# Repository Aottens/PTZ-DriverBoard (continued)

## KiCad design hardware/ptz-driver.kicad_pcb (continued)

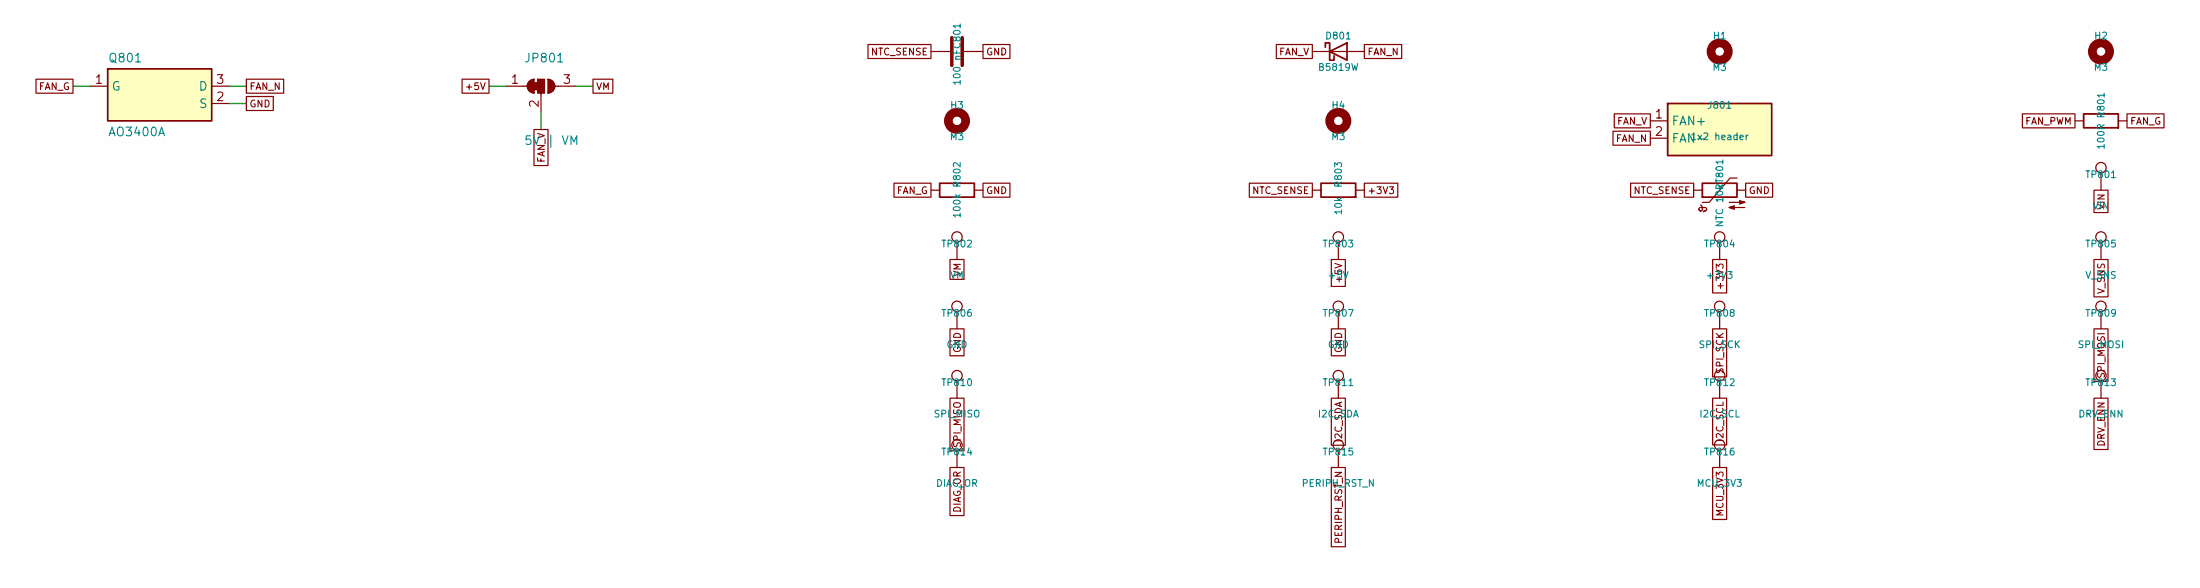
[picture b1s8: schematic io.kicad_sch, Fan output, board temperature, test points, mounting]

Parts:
C801: 100 nF; C_0603_1608Metric; LCSC C14663
D801: B5819W; D_SOD-123; MPN B5819W; LCSC C8598
H1, H2, H3, H4: M3; MountingHole_3.2mm_M3
J801: 1x2 header; PinHeader_1x02_P2.54mm_Vertical
JP801: 5V | VM; SolderJumper-3_P1.3mm_Bridged12_RoundedPad1.0x1.5mm
Q801: AO3400A; SOT-23; MPN AO3400A; LCSC C20917
R801: 100R; R_0603_1608Metric; LCSC C22775
R802: 100k; R_0603_1608Metric; LCSC C25803
R803: 10k; R_0603_1608Metric; LCSC C25804
RT801: NTC 10k; R_0603_1608Metric; MPN KNTC0603/10KF3950; LCSC C2892547
TP801: VIN; TestPoint_D1.5
TP802: VM; TestPoint_D1.5
TP803: +5V; TestPoint_D1.5
TP804: +3V3; TestPoint_D1.5
TP805: V_SNS; TestPoint_D1.5
TP806, TP807: GND; TestPoint_D1.5
TP808: SPI_SCK; TestPoint_D1.5
TP809: SPI_MOSI; TestPoint_D1.5
TP810: SPI_MISO; TestPoint_D1.5
TP811: I2C_SDA; TestPoint_D1.5
TP812: I2C_SCL; TestPoint_D1.5
TP813: DRV_ENN; TestPoint_D1.5
TP814: DIAG_OR; TestPoint_D1.5
TP815: PERIPH_RST_N; TestPoint_D1.5
TP816: MCU_3V3; TestPoint_D1.5

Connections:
+3V3: R803.2, TP804.1; also elsewhere on the board
DRV_ENN: TP813.1; also elsewhere on the board
FAN_G: Q801.1 (G), R801.2, R802.1
FAN_N: D801.2 (A), J801.2 (FAN-), Q801.3 (D)
FAN_PWM: R801.1; also elsewhere on the board
GND: C801.2, Q801.2 (S), R802.2, RT801.2, TP806.1, TP807.1; also elsewhere on the board
I2C_SCL: TP812.1; also elsewhere on the board
I2C_SDA: TP811.1; also elsewhere on the board
MCU_3V3: TP816.1; also elsewhere on the board
NTC_SENSE: C801.1, R803.1, RT801.1; also elsewhere on the board
PERIPH_RST_N: TP815.1; also elsewhere on the board
SPI_MISO: TP810.1; also elsewhere on the board
SPI_MOSI: TP809.1; also elsewhere on the board
SPI_SCK: TP808.1; also elsewhere on the board
VIN: TP801.1; also elsewhere on the board
VM: JP801.3 (B), TP802.1; also elsewhere on the board
V_SNS: TP805.1; also elsewhere on the board

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
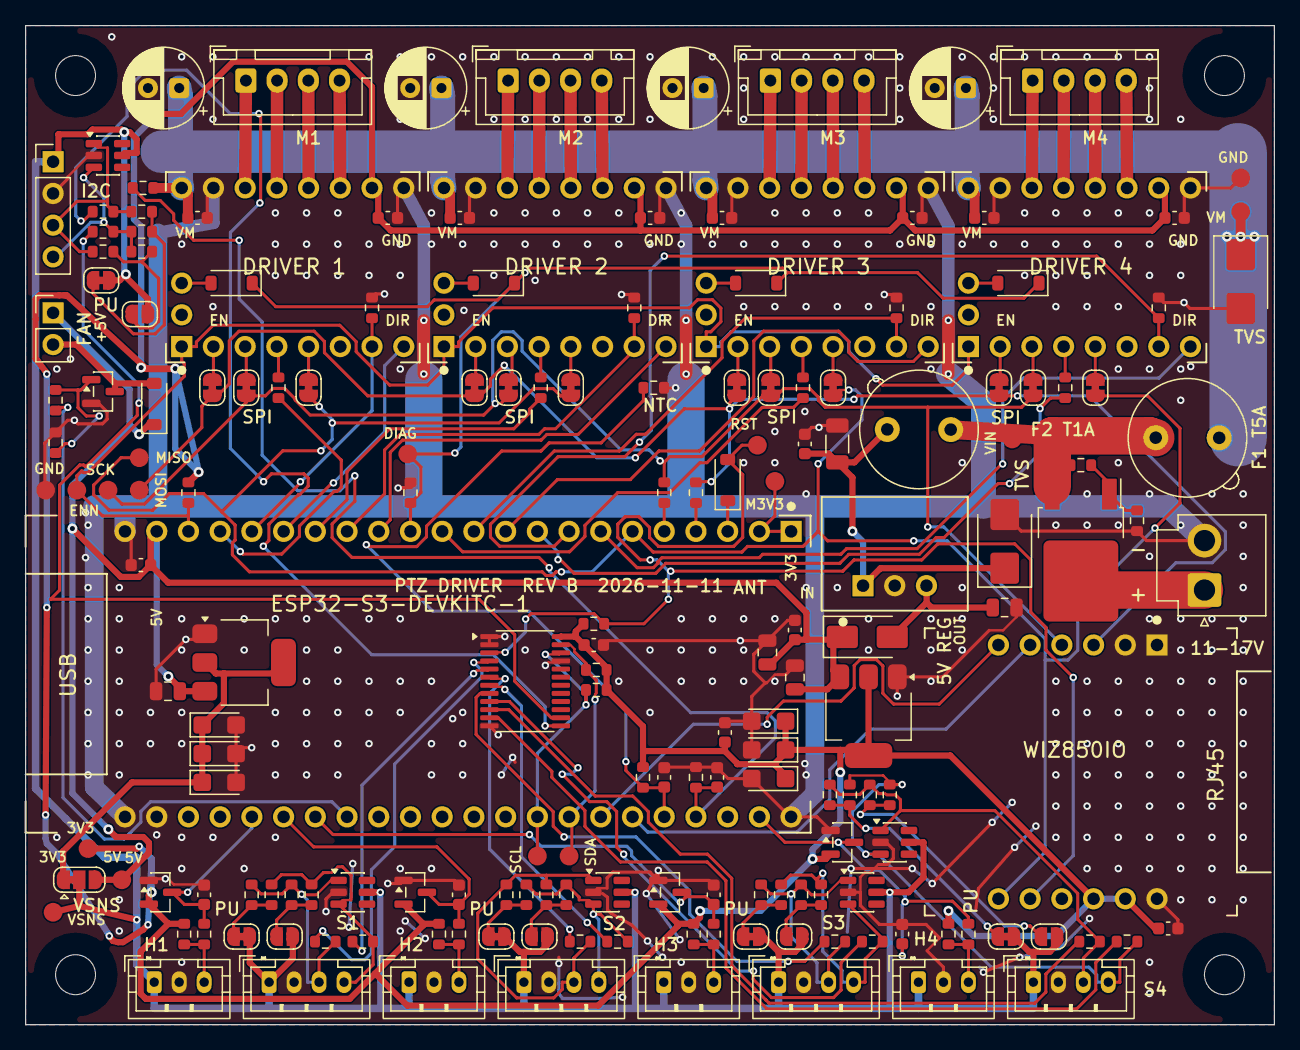
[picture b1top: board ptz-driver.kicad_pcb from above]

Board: 2 copper layers, 100.0 x 80.0 mm, 186 parts (0 on the bottom side), 116 nets.

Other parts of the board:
D103: SMBJ18A; D_SMB
R410, R610: 100k; R_0603_1608Metric

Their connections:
GND: D103.2, R410.2, R610.2; also elsewhere on the board
STEP2: R410.1; also elsewhere on the board
STEP4: R610.1; also elsewhere on the board
VIN_L: D103.1; also elsewhere on the board

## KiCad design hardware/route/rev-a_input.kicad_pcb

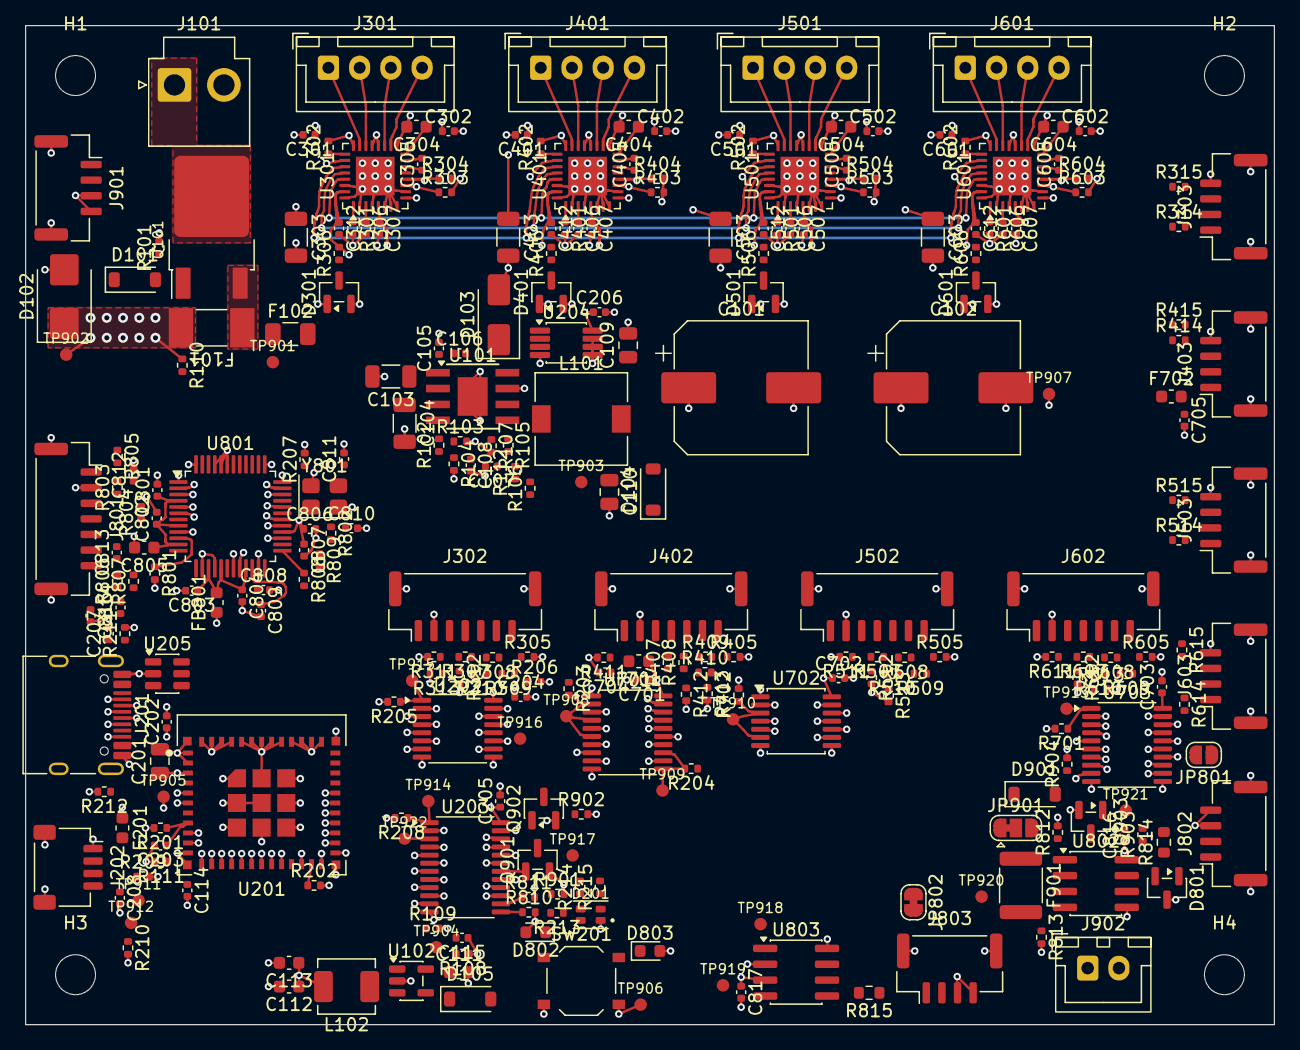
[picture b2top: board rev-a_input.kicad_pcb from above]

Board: 4 copper layers, 100.0 x 80.0 mm, 280 parts (0 on the bottom side), 199 nets.

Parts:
C101, C102: 220 µF 50 V; CP_Elec_10x10.5
C103, C104: 4.7 µF 50 V; C_1206_3216Metric
C105, C106, C301, C302, C401, C402, C501, C502, C601, C602: 100 nF 50 V; C_0402_1005Metric
C107, C812: 22 nF; C_0402_1005Metric
C108: 100 pF; C_0402_1005Metric
C109, C110: 22 µF 25 V; C_0805_2012Metric
C111: 4.7 µF 16 V; C_0603_1608Metric
C112, C113: 10 µF 10 V; C_0603_1608Metric
C114, C202, C204, C205, C206, C307, C407, C507, C607, C701, C702, C703, C801, C802, C803, C804, C806, C816, C817: 100 nF; C_0402_1005Metric
C115: 22 pF; C_0402_1005Metric
C201: 22 µF; C_0805_2012Metric
C203, C207, C208, C705: 1 µF; C_0402_1005Metric
C303, C403, C503, C603: 10 µF 50 V; C_1206_3216Metric
C304, C404, C504, C604: 1 µF 50 V; C_0603_1608Metric
C305, C405, C505, C605: 22 nF 50 V; C_0402_1005Metric
C306, C406, C506, C606, C704, C807, C808: 4.7 µF; C_0402_1005Metric
C312, C412, C512, C612: 1 nF; C_0402_1005Metric
C805: 10 µF; C_0603_1608Metric
C809, C815: 10 nF; C_0402_1005Metric
C810, C811: 18 pF; C_0402_1005Metric
C813, C814: 6.8 nF; C_0402_1005Metric
D101: 12 V zener; D_SOD-123
D102: SMBJ24A; D_SMB
D103: SS36; D_SMA
D104, D105, D901: B5819W; D_SOD-123
D201: RGB LED; LED_RGB_1616
D301, D401, D501, D601: BAT54S; SOT-23
D801: SM712; SOT-23
D802: LINK; LED_0603_1608Metric
D803: ACT; LED_0603_1608Metric
F101: 7 A slow; Fuse_Littelfuse-NANO2-451_453
F102: 1.5 A; Fuse_1206_3216Metric
F201, F701, F702: 0.2 A PTC; Fuse_0603_1608Metric
F901: 0.5 A PTC; Fuse_1812_4532Metric
FB801: 600R ferrite; L_0603_1608Metric
H1, H2, H3, H4: M3; MountingHole_3.2mm_M3
J101: B2P-VH; JST_VH_B2P-VH_1x02_P3.96mm_Vertical
J201: USB-C; USB_C_Receptacle_HRO_TYPE-C-31-M-12
J202: SM04B-SRSS-TB; JST_SH_SM04B-SRSS-TB_1x04-1MP_P1.00mm_Horizontal
J301, J401, J501, J601: B4B-XH-A; JST_XH_B4B-XH-A_1x04_P2.50mm_Vertical
J302, J402, J502, J602: BM07B-GHS-TBT; JST_GH_BM07B-GHS-TBT_1x07-1MP_P1.25mm_Vertical
J303, J403, J503, J603, J802, J901: SM04B-GHS-TB; JST_GH_SM04B-GHS-TB_1x04-1MP_P1.25mm_Horizontal
J801: SM07B-GHS-TB; JST_GH_SM07B-GHS-TB_1x07-1MP_P1.25mm_Horizontal
J803: BM04B-GHS-TBT; JST_GH_BM04B-GHS-TBT_1x04-1MP_P1.25mm_Vertical
J902: B2B-XH-A; JST_XH_B2B-XH-A_1x02_P2.50mm_Vertical
JP801: open; SolderJumper-2_P1.3mm_Open_RoundedPad1.0x1.5mm
JP802: bridged; SolderJumper-2_P1.3mm_Bridged_RoundedPad1.0x1.5mm
JP901: 5V | VM; SolderJumper-3_P1.3mm_Bridged12_RoundedPad1.0x1.5mm
L101: 22 µH; L_7.3x7.3_H4.5
L102: 2.2 µH; L_Sunlord_MWSA0402S
Q101: AOD4185; TO-252_JLC
Q901, Q902, Q903: AO3422; SOT-23
R101, R108, R110, R302, R311, R312, R313, R402, R411, R412, R413, R502, R511, R512, R513, R602, R611, R612, R613, R702, R901, R902, R904: 100k; R_0402_1005Metric
R102: 330k; R_0402_1005Metric
R103, R106: 47k; R_0402_1005Metric
R104: 220k; R_0402_1005Metric
R105: 4.7k; R_0402_1005Metric
R107, R111, R201, R202, R205, R206, R207, R208, R303, R304, R305, R403, R404, R405, R503, R504, R505, R603, R604, R605, R701, R810, R811, R812, R813: 10k; R_0402_1005Metric
R109, R306, R406, R506, R606: 22k; R_0402_1005Metric
R112, R211, R212: 5.1k; R_0402_1005Metric
R203, R204: 22R; R_0402_1005Metric
R209, R210: 2.2k; R_0402_1005Metric
R213, R808, R809: 1k; R_0402_1005Metric
R214, R215, R314, R315, R414, R415, R514, R515, R614, R615: 220R; R_0402_1005Metric
R301, R401, R501, R601: 12k; R_0402_1005Metric
R307, R308, R309, R407, R408, R409, R507, R508, R509, R607, R608, R609: 33R; R_0402_1005Metric
R310, R410, R510, R610, R903: 100R; R_0402_1005Metric
R801: 12.4k; R_0402_1005Metric
R802: 1M; R_0402_1005Metric
R803, R804, R806, R807: 49.9R; R_0402_1005Metric
R805: 10R; R_0402_1005Metric
R814, R815: 120R; R_0603_1608Metric
SW201: BOOT; SW_Push_1P1T_XKB_TS-1187A
TP901: VIN; TestPoint_D1.0
TP902: VM; TestPoint_D1.0
TP903: +5V; TestPoint_D1.0
TP904: VSYS; TestPoint_D1.0
TP905: +3V3; TestPoint_D1.0
TP906, TP907: GND; TestPoint_D1.0
TP908: SPI_SCK; TestPoint_D1.0
TP909: SPI_MOSI; TestPoint_D1.0
TP910: SPI_MISO; TestPoint_D1.0
TP911: I2C_SDA; TestPoint_D1.0
TP912: I2C_SCL; TestPoint_D1.0
TP913: DRV_ENN; TestPoint_D1.0
TP914: XINT_N; TestPoint_D1.0
TP915: CS_DRV_EN_N; TestPoint_D1.0
TP916: CS_SNS_EN_N; TestPoint_D1.0
TP917: SPARE; TestPoint_D1.0
TP918: CAN_TX; TestPoint_D1.0
TP919: CAN_RX; TestPoint_D1.0
TP920: RS485_TX; TestPoint_D1.0
TP921: RS485_RX; TestPoint_D1.0
TP922: EN; TestPoint_D1.0
U101: TPS54360; TI_SO-PowerPAD-8
U102: TLV62569; SOT-23-5
U201: ESP32-C6-MINI-1U-H4; ESP32-C6-MINI-1U
U202: SN74LVC139A; TSSOP-16_4.4x5mm_P0.65mm
U203: PCAL6416A; TSSOP-24_4.4x7.8mm_P0.65mm
U204: TMP1075; VSSOP-8_3x3mm_P0.65mm
U205: USBLC6-2SC6; SOT-23-6
U301, U401, U501, U601: TMC5240ATJ; QFN-32-1EP_5x5mm_P0.5mm_EP3.1x3.1mm
U701: SN74LVC244A; TSSOP-20_4.4x6.5mm_P0.65mm
U702: SN74LVC125A; TSSOP-14_4.4x5mm_P0.65mm
U703: SN74AHCT244; TSSOP-20_4.4x6.5mm_P0.65mm
U801: W5500; LQFP-48_7x7mm_P0.5mm
U802: SP3485; SOIC-8_3.9x4.9mm_P1.27mm
U803: SN65HVD230; SOIC-8_3.9x4.9mm_P1.27mm
Y801: 25 MHz; Crystal_SMD_3225-4Pin_3.2x2.5mm

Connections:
3V3A: C801.1, C802.1, C803.1, C804.1, C805.1, FB801.2, R803.2, R804.2, R805.1, U801.4, U801.8, U801.11, U801.15, U801.17, U801.21
+3V3: C112.1, C113.1, C115.1, C201.1, C202.1, C204.1, C205.1, C206.1, C307.1, C407.1, C507.1, C607.1, C701.1, C702.1, C806.1, C807.1, C816.1, C817.1, D201.4, D301.2, D401.2, D501.2, D601.2, D802.2, D803.2, F201.1, F701.1, FB801.1, L102.2, R108.1, R201.2, R202.2, R205.2, R206.2, R207.2, R208.2, R209.2, R210.2, R303.2, R304.2, R305.2, R403.2, R404.2, R405.2, R503.2, R504.2, R505.2, R603.2, R604.2, R605.2, R701.2, R810.2, R811.2, R813.2, TP905.1, U201.3, U202.16, U203.2, U203.24, U204.8, U301.5, U401.5, U501.5, U601.5, U701.20, U702.14, U801.28, U801.43, U801.44, U801.45, U802.8, U803.3
+3V3_I2C: C208.1, F201.2, J202.2
+3V3_SNS: C704.1, F701.2, J302.1, J402.1, J502.1, J602.1
+5V: C109.1, C110.1, C703.1, D104.2, F702.1, JP901.1, L101.2, R106.1, TP903.1, U703.20
+5V_EXT: C705.1, F702.2, J303.1, J403.1, J503.1, J603.1
A1_1V8: C306.1, U301.3
A1_CPI: C305.1, U301.14
A1_CPO: C305.2, U301.15
A1_IREF: R301.1, U301.1
A1_SLEEPN: R302.1, U301.25
A1_VCP: C304.1, U301.16
A2_1V8: C406.1, U401.3
A2_CPI: C405.1, U401.14
A2_CPO: C405.2, U401.15
A2_IREF: R401.1, U401.1
A2_SLEEPN: R402.1, U401.25
A2_VCP: C404.1, U401.16
A3_1V8: C506.1, U501.3
A3_CPI: C505.1, U501.14
A3_CPO: C505.2, U501.15
A3_IREF: R501.1, U501.1
A3_SLEEPN: R502.1, U501.25
A3_VCP: C504.1, U501.16
A4_1V8: C606.1, U601.3
A4_CPI: C605.1, U601.14
A4_CPO: C605.2, U601.15
A4_IREF: R601.1, U601.1
A4_SLEEPN: R602.1, U601.25
A4_VCP: C604.1, U601.16
BOOT: R202.1, SW201.1, U201.23
BUCK_BOOT: C106.1, U101.1
BUCK_COMP: C108.1, R105.1, U101.6
BUCK_COMP_RC: C107.1, R105.2
BUCK_EN: R102.2, R103.1, U101.3
BUCK_FB: R107.1, R112.2, U101.5
BUCK_FB_MID: R106.2, R112.1
BUCK_RT: R104.1, U101.4
BUCK_SW: C106.2, D103.1, L101.1, U101.8
CAN_H: J803.1, R815.1, U803.7
CAN_L: J803.2, JP802.2, U803.6
CAN_RX: TP919.1, U201.28, U803.4
CAN_TERM: JP802.1, R815.2
CAN_TX: TP918.1, U201.27, U803.1
CC1: J201.A5, R211.1
CC2: J201.B5, R212.1
CS_A0: U201.9, U202.2, U202.14
CS_A1: U201.10, U202.3, U202.13
CS_DRV1: U202.4, U301.26
CS_DRV2: U202.5, U401.26
CS_DRV3: U202.6, U501.26
CS_DRV4: U202.7, U601.26
CS_DRV_EN_N: R205.1, TP915.1, U201.12, U202.1
CS_SNS1: R309.1, U202.12, U702.1
CS_SNS2: R409.1, U202.11, U702.4
CS_SNS3: R509.1, U202.10, U702.10
CS_SNS4: R609.1, U202.9, U702.13
CS_SNS_EN_N: R206.1, TP916.1, U201.13, U202.15, U701.1, U701.19
DIAG0_1: R303.1, U203.4, U301.11, U703.2
DIAG0_2: R403.1, U203.5, U401.11, U703.4
DIAG0_3: R503.1, U203.6, U501.11, U703.6
DIAG0_4: R603.1, U203.7, U601.11, U703.8
DIAG1_1: R304.1, U203.8, U301.12, U703.11
DIAG1_2: R404.1, U203.9, U401.12, U703.13
DIAG1_3: R504.1, U203.10, U501.12, U703.15
DIAG1_4: R604.1, U203.11, U601.12, U703.17
DIR1_B: R315.1, U703.9
DIR1_O: J303.3, R315.2
DIR2_B: R415.1, U703.7
DIR2_O: J403.3, R415.2
DIR3_B: R515.1, U703.5
DIR3_O: J503.3, R515.2
DIR4_B: R615.1, U703.3
DIR4_O: J603.3, R615.2
DRV_ENN: R701.1, TP913.1, U201.26, U301.9, U401.9, U501.9, U601.9, U703.1, U703.19
EN: C203.1, R201.1, TP922.1, U201.8, U203.3
ETH_1V2: C809.1, U801.22
ETH_ACT: R809.1, U801.27
ETH_CS_N: R207.1, U201.19, U801.32
ETH_INT_N: R810.1, U203.13, U801.36
ETH_LED_A: D803.1, R809.2
ETH_LED_L: D802.1, R808.2
ETH_LINK: R808.1, U801.25
ETH_RCT: C815.1, J801.7, R806.2, R807.2
ETH_RDN: C814.2, J801.6
ETH_RDP: C813.2, J801.5
ETH_RES: R801.1, U801.10
ETH_RST_N: R811.1, U203.14, U801.37
ETH_RXN: C814.1, R807.1, U801.5
ETH_RXP: C813.1, R806.1, U801.6
ETH_TCT: C812.1, J801.1, R805.2
ETH_TOCAP: C808.1, U801.20
ETH_TXN: J801.4, R804.1, U801.1
ETH_TXP: J801.3, R803.1, U801.2
ETH_XI: C810.1, R802.1, U801.30, Y801.1
ETH_XO: C811.1, R802.2, U801.31, Y801.3
FAN_G: Q903.1, R903.2, R904.1
FAN_N: D901.2, J902.2, Q903.3
FAN_PWM: R903.1, U201.20
FAN_SRC: F901.1, JP901.2
FAN_V: D901.1, F901.2, J902.1
FB3V3: C115.2, R108.2, R109.1, U102.5
GND: C101.2, C102.2, C103.2, C104.2, C105.2, C107.2, C108.2, C109.2, C110.2, C111.2, C112.2, C113.2, C114.2, C201.2, C202.2, C203.2, C204.2, C205.2, C206.2, C207.2, C208.2, C301.2, C302.2, C303.2, C306.2, C307.2, C312.2, C401.2, C402.2, C403.2, C406.2, C407.2, C412.2, C501.2, C502.2, C503.2, C506.2, C507.2, C512.2, C601.2, C602.2, C603.2, C606.2, C607.2, C612.2, C701.2, C702.2, C703.2, C704.2, C705.2, C801.2, C802.2, C803.2, C804.2, C805.2, C806.2, C807.2, C808.2, C809.2, C810.2, C811.2, C812.2, C815.2, C816.2, C817.2, D102.2, D103.2, D301.1, D401.1, D501.1, D601.1, D801.3, J101.2, J201.A1, J201.A12, J201.B1, J201.B12, J201.SH, J202.1, J202.MP, J302.2, J302.MP, J303.4, J303.MP, J402.2, J402.MP, J403.4, J403.MP, J502.2, J502.MP, J503.4, J503.MP, J602.2, J602.MP, J603.4, J603.MP, J801.2, J801.MP, J802.3, J802.4, J802.MP, J803.3, J803.4, J803.MP, J901.3, J901.4, J901.MP, Q901.2, Q902.2, Q903.2, R101.2, R103.2, R104.2, R107.2, R109.2, R111.2, R211.2, R212.2, R301.2, R311.2, R312.2, R313.2, R401.2, R411.2, R412.2, R413.2, R501.2, R511.2, R512.2, R513.2, R601.2, R611.2, R612.2, R613.2, R702.2, R801.2, R812.2, R901.2, R902.2, R904.2, SW201.2, TP906.1, TP907.1, U101.7, U101.9, U102.2, U201.1, U201.2, U201.11, U201.14, U201.36, U201.37, U201.38, U201.39, U201.40, U201.41, U201.42, U201.43, U201.44, U201.45, U201.46, U201.47, U201.48, U201.49, U201.50, U201.51, U201.52, U201.53, U202.8, U203.12, U203.21, U204.4, U204.5, U204.6, U204.7, U205.2, U301.2, U301.4, U301.6, U301.7, U301.8, U301.10, U301.30, U301.32, U301.33, U401.2, U401.4, U401.6, U401.7, U401.8, U401.10, U401.30, U401.32, U401.33, U501.2, U501.4, U501.6, U501.7, U501.8, U501.10, U501.30, U501.32, U501.33, U601.2, U601.4, U601.6, U601.7, U601.8, U601.10, U601.30, U601.32, U601.33, U701.10, U702.7, U703.10, U801.3, U801.9, U801.14, U801.16, U801.19, U801.23, U801.29, U801.48, U802.5, U803.2, U803.8, Y801.2, Y801.4
HOME1: C312.1, D301.3, R306.2, U301.31
HOME1_IN: J302.7, R305.1, R306.1
HOME2: C412.1, D401.3, R406.2, U401.31
HOME2_IN: J402.7, R405.1, R406.1
HOME3: C512.1, D501.3, R506.2, U501.31
HOME3_IN: J502.7, R505.1, R506.1
HOME4: C612.1, D601.3, R606.2, U601.31
HOME4_IN: J602.7, R605.1, R606.1
I2C_SCL: J202.4, R210.1, TP912.1, U201.24, U203.22, U204.2
I2C_SDA: J202.3, R209.1, TP911.1, U201.22, U203.23, U204.1
LED_B_K: D201.3, R215.1
LED_B_N: R215.2, U203.17
LED_G_K: D201.2, R214.1
LED_G_N: R214.2, U203.16
LED_R_K: D201.1, R213.1
LED_R_N: R213.2, U203.15
M1_A1: J301.1, U301.23
M1_A2: J301.2, U301.22
M1_B1: J301.4, U301.18
M1_B2: J301.3, U301.19
M2_A1: J401.1, U401.23
M2_A2: J401.2, U401.22
M2_B1: J401.4, U401.18
M2_B2: J401.3, U401.19
M3_A1: J501.1, U501.23
M3_A2: J501.2, U501.22
M3_B1: J501.4, U501.18
M3_B2: J501.3, U501.19
M4_A1: J601.1, U601.23
M4_A2: J601.2, U601.22
M4_B1: J601.4, U601.18
M4_B2: J601.3, U601.19
REC: Q902.1, R902.1, U203.19
REC_OD: J901.2, Q902.3
RP_GATE: D101.2, Q101.1, R101.1
RS485_A: D801.1, J802.1, R814.1, U802.6
RS485_B: D801.2, J802.2, JP801.2, U802.7
RS485_DE: R812.1, U201.29, U802.2, U802.3
RS485_RX: R813.1, TP921.1, U201.30, U802.1
RS485_TERM: JP801.1, R814.2
RS485_TX: TP920.1, U201.31, U802.4
SNS1_CS: J302.6, R309.2
SNS1_MISO: J302.5, R310.1
SNS1_MISO_B: R310.2, R313.1, U702.2
SNS1_MOSI: J302.4, R308.2, R312.1
SNS1_SCK: J302.3, R307.2, R311.1
SNS2_CS: J402.6, R409.2
SNS2_MISO: J402.5, R410.1
SNS2_MISO_B: R410.2, R413.1, U702.5
SNS2_MOSI: J402.4, R408.2, R412.1
SNS2_SCK: J402.3, R407.2, R411.1
SNS3_CS: J502.6, R509.2
SNS3_MISO: J502.5, R510.1
SNS3_MISO_B: R510.2, R513.1, U702.9
SNS3_MOSI: J502.4, R508.2, R512.1
SNS3_SCK: J502.3, R507.2, R511.1
SNS4_CS: J602.6, R609.2
SNS4_MISO: J602.5, R610.1
SNS4_MISO_B: R610.2, R613.1, U702.12
SNS4_MOSI: J602.4, R608.2, R612.1
SNS4_SCK: J602.3, R607.2, R611.1
SNS_MOSI1_B: R308.1, U701.9
SNS_MOSI2_B: R408.1, U701.7
SNS_MOSI3_B: R508.1, U701.5
SNS_MOSI4_B: R608.1, U701.3
SNS_SCK1_B: R307.1, U701.18
SNS_SCK2_B: R407.1, U701.16
SNS_SCK3_B: R507.1, U701.14
SNS_SCK4_B: R607.1, U701.12
SPARE: TP917.1, U203.20
SPI_MISO: R702.1, TP910.1, U201.5, U301.29, U401.29, U501.29, U601.29, U702.3, U702.6, U702.8, U702.11, U801.34
SPI_MOSI: R204.2, TP909.1, U301.28, U401.28, U501.28, U601.28, U701.11, U701.13, U701.15, U701.17, U801.35
SPI_MOSI_MCU: R204.1, U201.16
SPI_SCK: R203.2, TP908.1, U301.27, U401.27, U501.27, U601.27, U701.2, U701.4, U701.6, U701.8, U801.33
SPI_SCK_MCU: R203.1, U201.15
STEP1_B: R314.1, U703.18
STEP1_O: J303.2, R314.2
STEP2_B: R414.1, U703.16
STEP2_O: J403.2, R414.2
STEP3_B: R514.1, U703.14
STEP3_O: J503.2, R514.2
STEP4_B: R614.1, U703.12
STEP4_O: J603.2, R614.2
SW3V3: L102.1, U102.3
TALLY: Q901.1, R901.1, U203.18
TALLY_OD: J901.1, Q901.3
USB_DN: J201.A7, J201.B7, U201.17, U205.1, U205.6
USB_DP: J201.A6, J201.B6, U201.18, U205.3, U205.4
VBUS: C207.1, D105.2, J201.A4, J201.A9, J201.B4, J201.B9, U205.5
VIN: D101.1, F101.1, F102.1, Q101.3, TP901.1
VIN_L: C103.1, C104.1, C105.1, F102.2, R102.1, U101.2
VIN_RAW: J101.1, Q101.2
VM: C101.1, C102.1, C301.1, C302.1, C303.1, C304.2, C401.1, C402.1, C403.1, C404.2, C501.1, C502.1, C503.1, C504.2, C601.1, C602.1, C603.1, C604.2, D102.1, F101.2, JP901.3, R110.1, R302.2, R402.2, R502.2, R602.2, TP902.1, U301.17, U301.20, U301.21, U301.24, U401.17, U401.20, U401.21, U401.24, U501.17, U501.20, U501.21, U501.24, U601.17, U601.20, U601.21, U601.24
VM_SENSE: C114.1, R110.2, R111.1, U201.6
VSYS: C111.1, D104.1, D105.1, TP904.1, U102.1, U102.4
XINT_N: R208.1, TP914.1, U201.25, U203.1

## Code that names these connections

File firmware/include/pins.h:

// Pin assignments of the PTZ driver board, Rev B. The single source for pins.
//
// hardware/tools/circuit.py builds the schematic from this file and hardware/check_netlist.py checks the
// netlist against it, so firmware and board cannot disagree. Change a pin here and nowhere else.
//
// Format, one per line and parsed by those scripts:  #define PIN_<NET> <gpio>
// The MCU is an ESP32-S3-DevKitC-1U on headers. A net ending in _N is active low.
//
// Rules behind this table (specs/modules/control.md, CTL-08):
//  - GPIO35, 36, 37 are not used: on boards with octal memory (N8R8, N16R8) they belong to the module.
//  - GPIO38 and GPIO48 carry the board's RGB LED (v1.1 and v1.0); GPIO38 is left free, GPIO48 gets a slow input.
//  - GPIO0 (BOOT), GPIO19/20 (USB) and GPIO44 (driven by the USB-UART bridge) are not used.
//  - GPIO43 prints the ROM's boot log, so it only reads a home input, behind a 10 k resistor.
//  - GPIO45 must be low at reset: it drives the fan switch, whose gate has a pull-down.
//  - GPIO46 must be low to enter download mode: it carries DIR2, never the fault line.
//  - Analog inputs are on ADC1 (GPIO1 to 10), which works with WiFi on.
#pragma once

// Header J1, from the antenna end towards USB -------------------------------------------------

// SPI bus shared by the four driver sockets (TMC2240, mode 3) and the Ethernet module (W5500)
#define PIN_SPI_MOSI 4
#define PIN_SPI_SCK 5
#define PIN_SPI_MISO 6

// Axis 4 (focus)
#define PIN_DIR4 7
#define PIN_STEP4 15
#define PIN_DRV4_CS 16
// Axis 3 (zoom)
#define PIN_DIR3 17
#define PIN_STEP3 18
#define PIN_DRV3_CS 8
// Stall or fault of any driver, high = active. Ask the drivers over their bus which one.
// A TMC2240's DIAG0 is open drain after reset and cannot raise this line: set diag0_pushpull in GCONF first.
#define PIN_DIAG_OR 3
// Axis 2 (tilt). GPIO46 must be low to enter download mode: a direction line is, a fault line may not be.
#define PIN_DIR2 46
#define PIN_STEP2 9
#define PIN_DRV2_CS 10
// Axis 1 (pan)
#define PIN_DIR1 11
#define PIN_STEP1 12
#define PIN_DRV1_CS 13

// Motor enable for all four drivers. High = off; pulled up on the board and on every module.
#define PIN_DRV_ENN 14

// Header J3, from the antenna end towards USB -------------------------------------------------

// Home inputs, low = switch closed. HOME4 shares its pin with the ROM's boot log (see above).
#define PIN_HOME4 43
// Motor supply after its fuse, divided by 11 (100k / 10k). ADC1 channel 0.
#define PIN_VM_SENSE 1
// Board temperature: 10k NTC to ground, 10k to 3.3 V. ADC1 channel 1.
#define PIN_NTC_SENSE 2
// Ethernet module
#define PIN_ETH_CS_N 42
#define PIN_ETH_INT_N 41
// I2C to the multiplexer (TCA9548A at 0x70): channel 0-3 = sensor port 1-4, channel 4 = spare header
#define PIN_I2C_SDA 40
#define PIN_I2C_SCL 39
// Fan output, high = on
#define PIN_FAN_PWM 45
#define PIN_HOME3 48
#define PIN_HOME2 47
#define PIN_HOME1 21

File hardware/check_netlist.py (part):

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    for n in ("VM_SENSE", "NTC_SENSE"):
        if n in pins and not 1 <= pins[n] <= 10:
            flag(n + " not ADC1", "%s on GPIO1..10, is GPIO%d" % (n, pins[n]))
    if pins.get("FAN_PWM") != 45:
        flag("FAN_PWM not GPIO45", "FAN_PWM on GPIO45")
    if pins.get("DIAG_OR") != 3:
        flag("DIAG_OR not GPIO3", "DIAG_OR on GPIO3")
    for g in (43, 48):
        for n in by_gpio.get(g, []):
            if not n.startswith("HOME"):
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
# ================================================================ POWER (specs/modules/power.md)
def pow_01_input():
    """POW-01. J101 JST B2P-VH: pin 1 VIN_RAW (plus), pin 2 GND."""
    return {("J101", "1"): "VIN_RAW", ("J101", "2"): "GND"}


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

def enc_07_esd():
    """ENC-07. One SRV05-4 (SOT-23-6) per port: SDA on pin 1, SCL on pin 3, pins 4 and 6 open, 2 GND, 5 V_SNS.
    Ua01 for sensor port n, U702 for the spare port."""
    d = {}
    for n, a in AXES:
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

def ctl_08_pin_table():
    """CTL-08. Every usable A201 GPIO pad carries the net pins.h gives it (SPI_SCK, SPI_MOSI as *_MCU), or none;
    plus what CTL-08 demands of pins.h itself."""
    pins = parse_pins_h()
    inv = {g: n for n, g in pins.items()}
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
